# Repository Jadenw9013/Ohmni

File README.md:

# Ohmni

**Build circuits. Understand why.**

Ohmni is an AI electronics engineering mentor. It turns supported product ideas
into inspectable circuit plans, KiCad schematics, routed boards and manufacturing
artifacts. **LLMs propose; evidence grounds; deterministic systems verify.**
Each result says which checks actually ran and what remains unknown. A software
check is not a hardware bench test or a guarantee that a board is ready to build.

## Start here

| Your goal | Start with |
|---|---|
| See the product without accounts or native tools | Saved demo below |
| Develop with teammates | [Setup guide](docs/TEAM_SETUP.md) |
| Give a coding AI useful context | [AI teammate handoff](docs/AI_TEAMMATE_HANDOFF.md) and [AGENTS.md](AGENTS.md) |
| Understand the engineering boundaries | [Architecture](ARCHITECTURE.md), [verification](VERIFICATION.md), [decisions](docs/DECISIONS.md) |
| Find current approved work | `.ai/state.yaml`, then `python scripts/ai_state.py next` |

## October 2026 hackathon

Start with the [Fetch.ai implementation and setup guide](docs/hackathon/FETCH_AI_IMPLEMENTATION_PLAN.md)
for the weekend scope, local commands, integration checklist and fallback.
The Fetch adapter supports reviewed board generation and private downloads directly
in ASI:One, plus an optional main Ohmni UI with saved projects, persistent
board/component chat and reviewed revision editing. See [using Ohmni in ASI:One](docs/hackathon/FETCH_AGENT_SETUP.md). Paper redesign and new Sentry prize work
are deferred; the existing disabled telemetry core remains available.
See [research and readiness](docs/hackathon/RESEARCH_AND_READINESS.md) for eligibility
and submission details, and [assistant coordination](docs/hackathon/ASSISTANT_WORKFLOW.md)
for Codex, Claude and Antigravity assignments. Run `python scripts/hackathon_preflight.py`
from the project venv for a local setup check.
Every teammate should follow the [engineering tool setup](docs/LOCAL_ENGINEERING_SETUP.md)
for the pinned native tools and run the included verification after pulling.
Start with `python3.13 scripts/setup_hackathon.py` on macOS/Linux or
`py -3.13 scripts/setup_hackathon.py` on Windows. This prepares `.venv` and checks
dependencies without starting an agent. Use the [troubleshooting guide](docs/hackathon/TROUBLESHOOTING.md)
and [submission template](docs/hackathon/SUBMISSION_TEMPLATE.md) during the event.
Once tools are installed, run `python scripts/rehearse_hackathon.py` from the venv
for one fresh local demo readiness report, including board and browser checks.

For the physical companion, use the [Stack-chan developer handoff](docs/hackathon/STACKCHAN_HANDOFF.md):
hardware setup, team ownership, a versioned USB connector contract, a Claude
assignment and full-flow acceptance checks. This is an implementation handoff;
robot and speech connectors are not yet shipped.

### Fetch track: try the primary workflow in ASI:One

**Agent:** Ohmni PCB Guide (`@ohmni-pcb-guide`)

**Address:** `agent1qvzucpk72r48d4gys9npx2an8jjj5mqpzwfjz4yt6a7mnqyag5gzqm5dc32`

[Chat in ASI:One](https://asi1.ai/ai/agent1qvzucpk72r48d4gys9npx2an8jjj5mqpzwfjz4yt6a7mnqyag5gzqm5dc32)
· [Agentverse profile](https://agentverse.ai/agents/details/agent1qvzucpk72r48d4gys9npx2an8jjj5mqpzwfjz4yt6a7mnqyag5gzqm5dc32/profile)

1. Keep Ohmni PCB Guide selected as the recipient. Ask: **“I want a USB-powered
   board to measure the temperature and humidity in my room.”**
2. Answer any necessary questions. Review the proposed components, dimensions,
   assembly needs and limitations, then send the exact displayed `CONFIRM` code.
3. Receive actual build progress and findings in the same conversation. `STATUS`
   checks the existing run; it does not generate another board.
4. Click the ZIP download delivered in chat, or send `FILES` for a fresh link.
   No custom frontend is needed to plan, confirm, generate or obtain the files.
5. Ask about the findings or request a supported change. A changed design needs
   a new review and exact confirmation. `OPEN` optionally connects the same project
   to Ohmni's 3D workspace; this is not a prerequisite for the ASI workflow.

**Integration:** a Python uAgents agent implements Agent Chat Protocol (ACP),
receives ASI requests and orchestrates Ohmni's existing planner, project store,
KiCad generation/checks and artifact release. Anthropic supplies planning and
explanations; engineering verdicts come from deterministic tools. One agent is
implemented; multi-agent orchestration, Payment Protocol and Interactive Cards
are not claimed. The original engineering platform predates this hackathon;
the Fetch integration and event work must be attributed separately in the submission.

**Run/test resources:** Python 3.13, pinned `uagents==0.26.1` /
`uagents-core==0.4.12`, KiCad 10.0.5 with libraries, ngspice 42 for supported
simulation, a privately configured Anthropic API key, stable agent seed, HTTPS
endpoint and persistent storage. See [exact setup and tests](docs/hackathon/FETCH_AGENT_SETUP.md)
and [native-tool installation](docs/LOCAL_ENGINEERING_SETUP.md). Hosted use needs
an ASI account; a local offline test does not require registering another agent.

See [ASI acceptance evidence and remaining submission items](docs/hackathon/ASI_TRACK_ACCEPTANCE.md)
and [submission template](docs/hackathon/SUBMISSION_TEMPLATE.md). Design files are
for human review; firmware, assembly and physical testing remain separate.

## Five-minute saved demo

Install Git and Python 3.12 or newer (3.13 is used by CI), then:

```text
git clone https://github.com/Jadenw9013/Ohmni.git
cd Ohmni
python scripts/serve_offline_demo.py
```

On Windows, use `py -3.13` if `python` is unavailable; on macOS/Linux use
`python3.13`. Open **http://127.0.0.1:8765/**. Stop with Ctrl+C.
No pip install, API key, KiCad, ngspice, Node or cloud account is needed for this
path. All required saved-demo assets are committed.

This replays a saved board, a deliberately damaged copy and its recorded DRC
finding, and the restored original. It does **not** generate a new board or run
live simulation. [Hosting and rehearsal details](docs/hackathon/DEMO_SITE_INTEGRATION.md).

## Local development

Use the [copyable OS-specific commands](docs/TEAM_SETUP.md#development-setup).
The short version, after creating and activating a virtual environment, is:

```text
python -m pip install -e ".[dev]"
python scripts/ai_state.py validate
python scripts/demo_server.py
```

Open **http://127.0.0.1:8765/#workspace**. Guided setup and saved-demo exploration
work without a provider key; free-text AI planning requires a separately supplied
Anthropic key and can incur charges. New board generation needs KiCad. Installing
the Python package does not install native EDA tools.

## What is supported today

- Three bounded USB-powered ESP32 families: I2C sensors, buttons/lights, and SPI
  peripherals. Free text is translated into supported choices, not arbitrary
  electronics. Battery-powered designs and arbitrary component admission are not
  implied by the chat UI.
- Deterministic electrical rules, placement/routing checks and independent KiCad
  ERC/DRC. Fabrication downloads remain tied to the recorded checks and lineage.
- SPICE for supported component bindings and analyses. Missing models block a
  simulation; **not every generated board can be simulated as a whole**.
- A vanilla JavaScript workspace and 3D board explorer; local SQLite persistence.
- Fabrication assumptions and example BOM prices can be synthetic. There is no
  pick-and-place/CPL export or automatic firmware generation. Saved results are
  not physical measurements.

See the [PCB explorer guide](docs/PCB_EXPLORER.md) for the landing board's scope.
The [product documents](docs/product/README.md) describe proposed work; they are
not evidence that those features are implemented or approved.

## Built at LA AI Hackathon 2026

Ohmni existed before AI Hackathon 2026 by LA Hacks (October 17-18, 2026). Every
feature described above this section is pre-existing work. Only the features
listed here were built during the event, and only these should be judged.

<!-- Fill in during the event: feature, what it does, and the commits or PR that built it. -->

- **Stack-chan desk tutor** ([plan](docs/hackathon/STACKCHAN_TUTOR_PLAN.md),
  [`tools/stackchan`](tools/stackchan/README.md), scope `STACKCHAN-TUTOR-1`, branch
  `claude/stackchan-tutor-proposal`). An M5Stack StackChan robot next to the screen
  narrates the board you open in the Ohmni workspace, and you can talk to it:
  - Custom robot firmware: USB JSON protocol, servos with stall protection, face, LEDs,
    head-touch double tap, speaker and microphone streaming.
  - An opt-in, loopback-only link in the workspace (`apps/web/robot-link.js`). The page
    shares a read-only description of the board and accepts only view-only commands.
  - The robot narrates Ohmni's deterministic board tour, highlighting each step. Double-tap
    its head to pause it and ask a question. Questions go through Ohmni's existing component
    tutor (live-verified), so the robot holds no AI key.
  - Spoken view commands ("show me the regulator", "isolate it", "what does it connect to",
    "zoom out"). Clicking a part on screen makes the robot name it.
  - Not done: design changes by voice (ST-T05, proposed only). Speech recognition with a
    real voice has not yet been bench-tested. The robot never confirms a design change.

## Contributing and AI tools

Follow [the teammate workflow](docs/TEAM_SETUP.md#working-together). Work on a
branch from current `origin/main`, preserve others' changes, and open a PR.
Do not commit secrets, private datasheets, local databases or generated receipts.

The optional [MCP server](docs/MCP_SERVER.md) requires `pip install -e ".[dev,mcp]"`.
It exposes the catalog and deterministic semantic verifier over local stdio;
it does not run AI, KiCad or SPICE. Coding assistants should first read
[AGENTS.md](AGENTS.md), not infer permission from a roadmap or an MCP connection.

## Repository housekeeping

- `src/ohmni/` and `apps/web/` contain the runtime; `scripts/` contains authoring,
  verification and rehearsal entrypoints. A script without imports is not
  necessarily unused: many are launched directly.
- `docs/`, `.ai/`, root implementation proposals and `ohmni_reference_visual_plan/`
  retain design history or evidence. Use the Start here links above for current
  onboarding; historical proposals do not authorize new work.
- The landing prototype/redesign directories remain test inputs and visual
  fingerprint dependencies. They are not interchangeable with the current
  controller landing page. Do not delete them just because they look old.
- The saved demo under `apps/web/hackathon-demo/` is a published copy of
  `examples/hackathon-demo/`, maintained by `scripts/sync_hackathon_demo.mjs`.
  Keep both: one serves the browser; the other preserves the source bundle.
- `.venv/`, `node_modules/`, `build/`, local `.worktrees/` and OS metadata are local
  development files, not files to transfer to a teammate. Some files under `out/`
  are deliberately tracked evidence despite the ignore rule; do not bulk-delete
  that directory or run `git clean -fdx` to tidy a working machine.

The unused 1.92 MB `apps/web/landing-board.png` concept image was retired after
its UI replacement. Historical checkpoint mentions remain historical; retrieve
it from Git history if needed. Its obsolete server startup requirement was
removed with it. No saved project, research source or behavior receipt was removed.

## License

Ohmni is released under the [MIT License](LICENSE). Bundled third-party files keep
their own licenses, for example `apps/web/vendor/THREE-LICENSE.txt`,
`apps/web/vendor/SENTRY-LICENSE.txt`, and the KiCad library footprints copied
under `fixtures/` and `examples/`, which remain under the KiCad libraries' license.

For the integrated USB voice-recorder family, firmware, simulation and physical-test boundaries, see [Voice recorder](docs/recorder/README.md).

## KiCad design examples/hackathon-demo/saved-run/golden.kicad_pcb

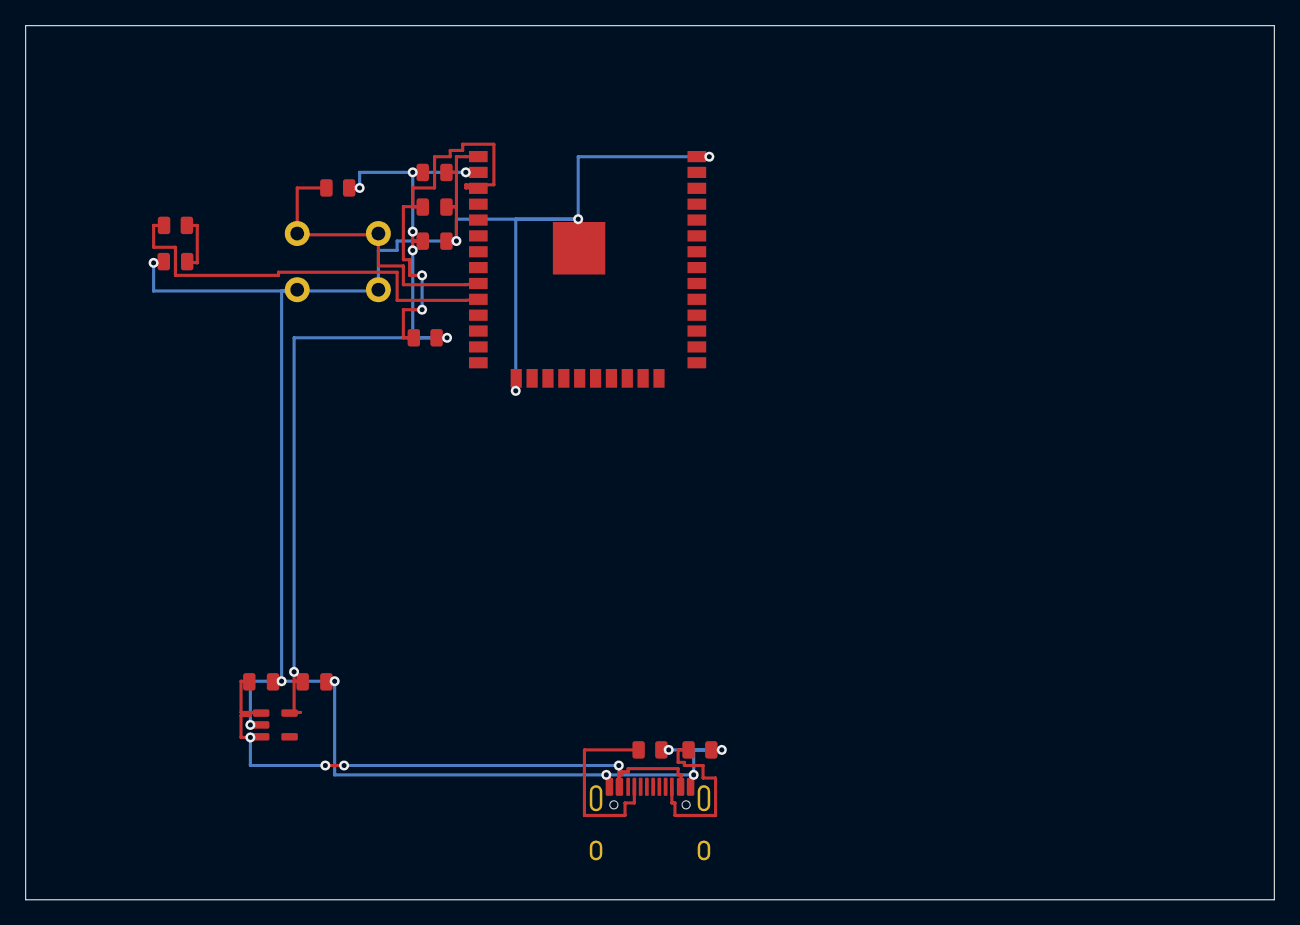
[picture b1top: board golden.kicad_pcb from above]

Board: 2 copper layers, 100.0 x 70.0 mm, 15 parts (0 on the bottom side), 9 nets.

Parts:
C1: GENERIC_CAPACITOR; ohmni_generated_C1
C2: GENERIC_CAPACITOR; ohmni_generated_C2
C3: GENERIC_CAPACITOR; ohmni_generated_C3
C4: GENERIC_CAPACITOR; ohmni_generated_C4
C5: GENERIC_CAPACITOR; ohmni_generated_C5
D1: GENERIC_LED_GREEN; ohmni_generated_D1
J1: USB_C_RECEPTACLE_16P; ohmni_generated_J1
R1: GENERIC_RESISTOR; ohmni_generated_R1
R2: GENERIC_RESISTOR; ohmni_generated_R2
R3: GENERIC_RESISTOR; ohmni_generated_R3
R10: GENERIC_RESISTOR; ohmni_generated_R10
R20: GENERIC_RESISTOR; ohmni_generated_R20
SW1: GENERIC_MOMENTARY_BUTTON; ohmni_generated_SW1
U1: ESP32-WROOM-32E; ohmni_generated_U1
U2: AP2112K-3.3TRG1; ohmni_generated_U2

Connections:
3V3: C2.1, C3.1, C4.1, R3.2, R20.2, U1.2, U2.5
BUTTON1: R20.1, SW1.1, U1.9
CC1: J1.A5, R1.1
CC2: J1.B5, R2.1
EN: C5.1, R3.1, U1.3
GND: C1.2, C2.2, C3.2, C4.2, C5.2, D1.1, J1.A1, J1.A12, J1.B1, J1.B12, R1.2, R2.2, SW1.2, U1.1, U1.15, U1.38, U1.39, U2.2
LED1_A: D1.2, R10.2
LED1_DRIVE: R10.1, U1.10
VBUS: C1.1, J1.A4, J1.A9, J1.B4, J1.B9, U2.1, U2.3
